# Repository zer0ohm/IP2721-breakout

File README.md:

# [BETA] IP2721-breakout
Breakout for IP2721 Sink-side USB PD Controller

## Pinout

| Pinname | I/O | Description                                    |
|---------|-----|------------------------------------------------|
| CC2     | I/O | Type-C Configuration Channel 2                 |
| CC1     | I/O | Type-C Configuration Channel 1                 |
| SEL     | I   | VBUS Voltage Select                            |
| VBG     | O   | Gate Driver for Load Switch MOSFET             |
| VOUT    | P   | VBUS Output                                    |
| GND     | P   | Ground                                         |
| TP1/PMG | O   | PMOS Gate Pulse Probing Point(Side B only)     |

## Usage
Soldering the parts obtained according to the [BOM](./PDBreakout_BOM.pdf) and configure the output voltage of the PD with "SEL_STAT".
* __IMPORTANT: MUST populate 5.1kΩ resistor to CCx, then configure SEL_STAT before power input.__

| SEL_STAT Voltage | Connected Terminals | Output VBUS Voltage |
|------------------|---------------------|---------------------|
| High             | High/H to COM/C     | 20V or 12V          |
| Float            | Do not put jumper   | 15V or 9V           |
| Low              | Low/L to COM/C      | 5V                  |

Note: VBUS voltage is 12/9/5V for IP2721-MAX12

## License
[CC BY-SA 4.0](https://creativecommons.org/licenses/by-sa/4.0/legalcode)

## Disclaimer
There is no warranty, expressed or implied, associated with files in this project. Please use at your own risk.

## Related Document
[IP2721 Datasheet](https://datasheet.lcsc.com/lcsc/2006111335_INJOINIC-IP2721_C603176.pdf)  
[Side A PartMap](./PDBreakout_PartMap_SideA.pdf)  
[Side B PartMap](./PDBreakout_PartMap_SideB.pdf)

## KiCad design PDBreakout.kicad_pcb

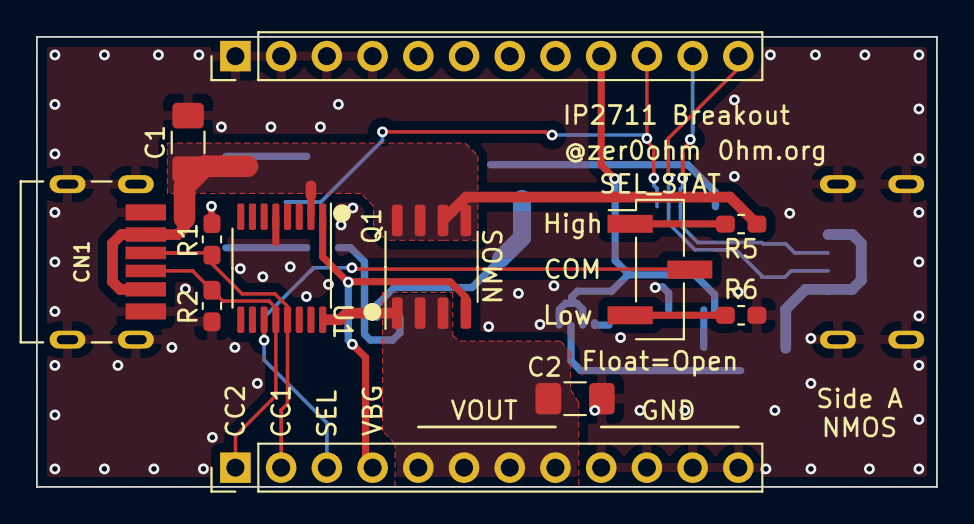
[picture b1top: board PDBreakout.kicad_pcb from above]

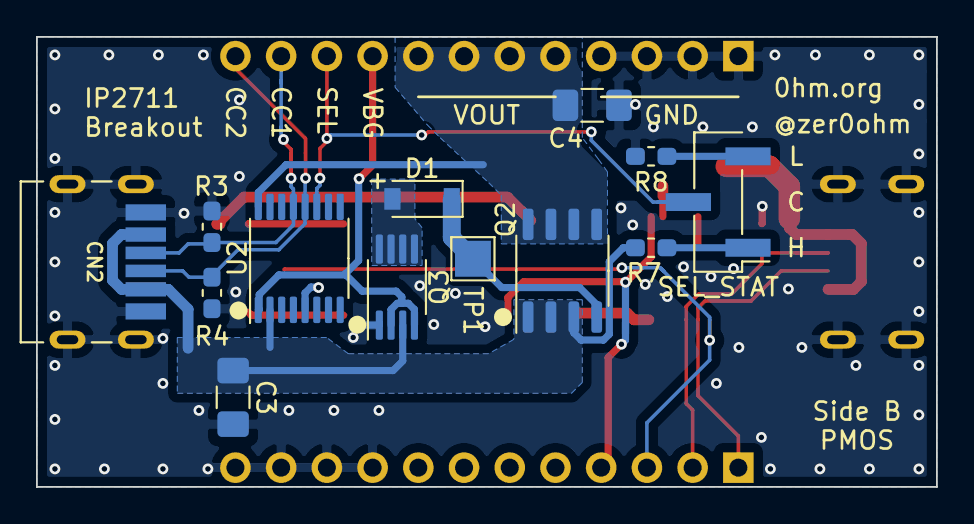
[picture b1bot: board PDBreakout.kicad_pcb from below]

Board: 2 copper layers, 50.0 x 25.0 mm, 25 parts (13 on the bottom side), 19 nets.

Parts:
C1, C3: 2.2u; C_1206_3216Metric_Pad1.42x1.75mm_HandSolder
C2, C4: 10u; C_1206_3216Metric_Pad1.42x1.75mm_HandSolder
CN1: UJC-HP-3-SMT-TR; CUI_UJC-HP-3-SMT-TR
CN2: UJC-HP-3-SMT-TR; CUI_UJC-HP-3-SMT-TR_HandSoldering
CN3, CN4: Conn_01x12; PinHeader_1x12_P2.54mm_Vertical
D1: 1N4148; D_SOD-123
JP1, JP2: SEL_STAT; PinHeader_1x03_P2.54mm_Vertical_SMD_Pin1Left
Q1: DMN4800LSS; SO-8_3.9x4.9mm_P1.27mm
Q2: SI4435DY; SO-8_3.9x4.9mm_P1.27mm
Q3: IRF7509; MSOP-8_3x3mm_P0.65mm
R1, R2, R3, R4: DNP; R_0603_1608Metric_Pad1.05x0.95mm_HandSolder
R5, R6, R7, R8: 100k; R_0603_1608Metric_Pad1.05x0.95mm_HandSolder
TP1: PMG; TestPoint_Pad_2.0x2.0mm
U1, U2: IP2721; TSSOP-16_4.4x5mm_P0.65mm

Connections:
/CC1_A: CN1.A5, CN3.2, R1.1, U1.13
/CC1_B: CN2.A5, CN4.11, R3.1, U2.13
/CC2_A: CN1.B5, CN3.1, R2.1, U1.12
/CC2_B: CN2.B5, CN4.12, R4.1, U2.12
/PMOS: D1.1, Q2.2, TP1.1
/SEL_A: CN3.3, JP1.2, U1.11
/SEL_B: CN4.10, JP2.2, U2.11
/VBG_A: CN3.4, Q1.2, U1.1
/VBG_B: CN4.9, Q3.2, Q3.4, U2.1
/VBUS_A: C1.1, CN1.B9, Q1.3, R5.1, U1.2
/VBUS_B: C3.1, CN2.B9, Q2.1, Q3.3, R7.1, U2.2
/VOUT_A: C2.1, CN3.5, CN3.6, CN3.7, CN3.8, Q1.1, U1.16
/VOUT_B: C4.1, CN4.5, CN4.6, CN4.7, CN4.8, Q2.3, U2.16
GND: C1.2, C2.2, C3.2, C4.2, CN1.A12, CN1.B12, CN1.S1, CN2.A12, CN2.B12, CN2.S1, CN3.9, CN3.10, CN3.11, CN3.12, CN4.1, CN4.2, CN4.3, CN4.4, Q3.1, R1.2, R2.2, R3.2, R4.2, R6.2, R8.2, U1.5, U2.5
unnamed: D1.2, Q3.5, Q3.6, Q3.7, Q3.8
unnamed: JP1.1, R5.2
unnamed: JP1.3, R6.1
unnamed: JP2.1, R7.2
unnamed: JP2.3, R8.1

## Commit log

2022-03-12 add License
2022-03-13 fix bom link
2022-04-11 "Usage"に追記
